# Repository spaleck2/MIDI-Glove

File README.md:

# MIDI-Glove
Eagle schematics and board layouts

This is a repository to share our schematics and board layouts so that we can help eachother out with design and each have access to all of the files.

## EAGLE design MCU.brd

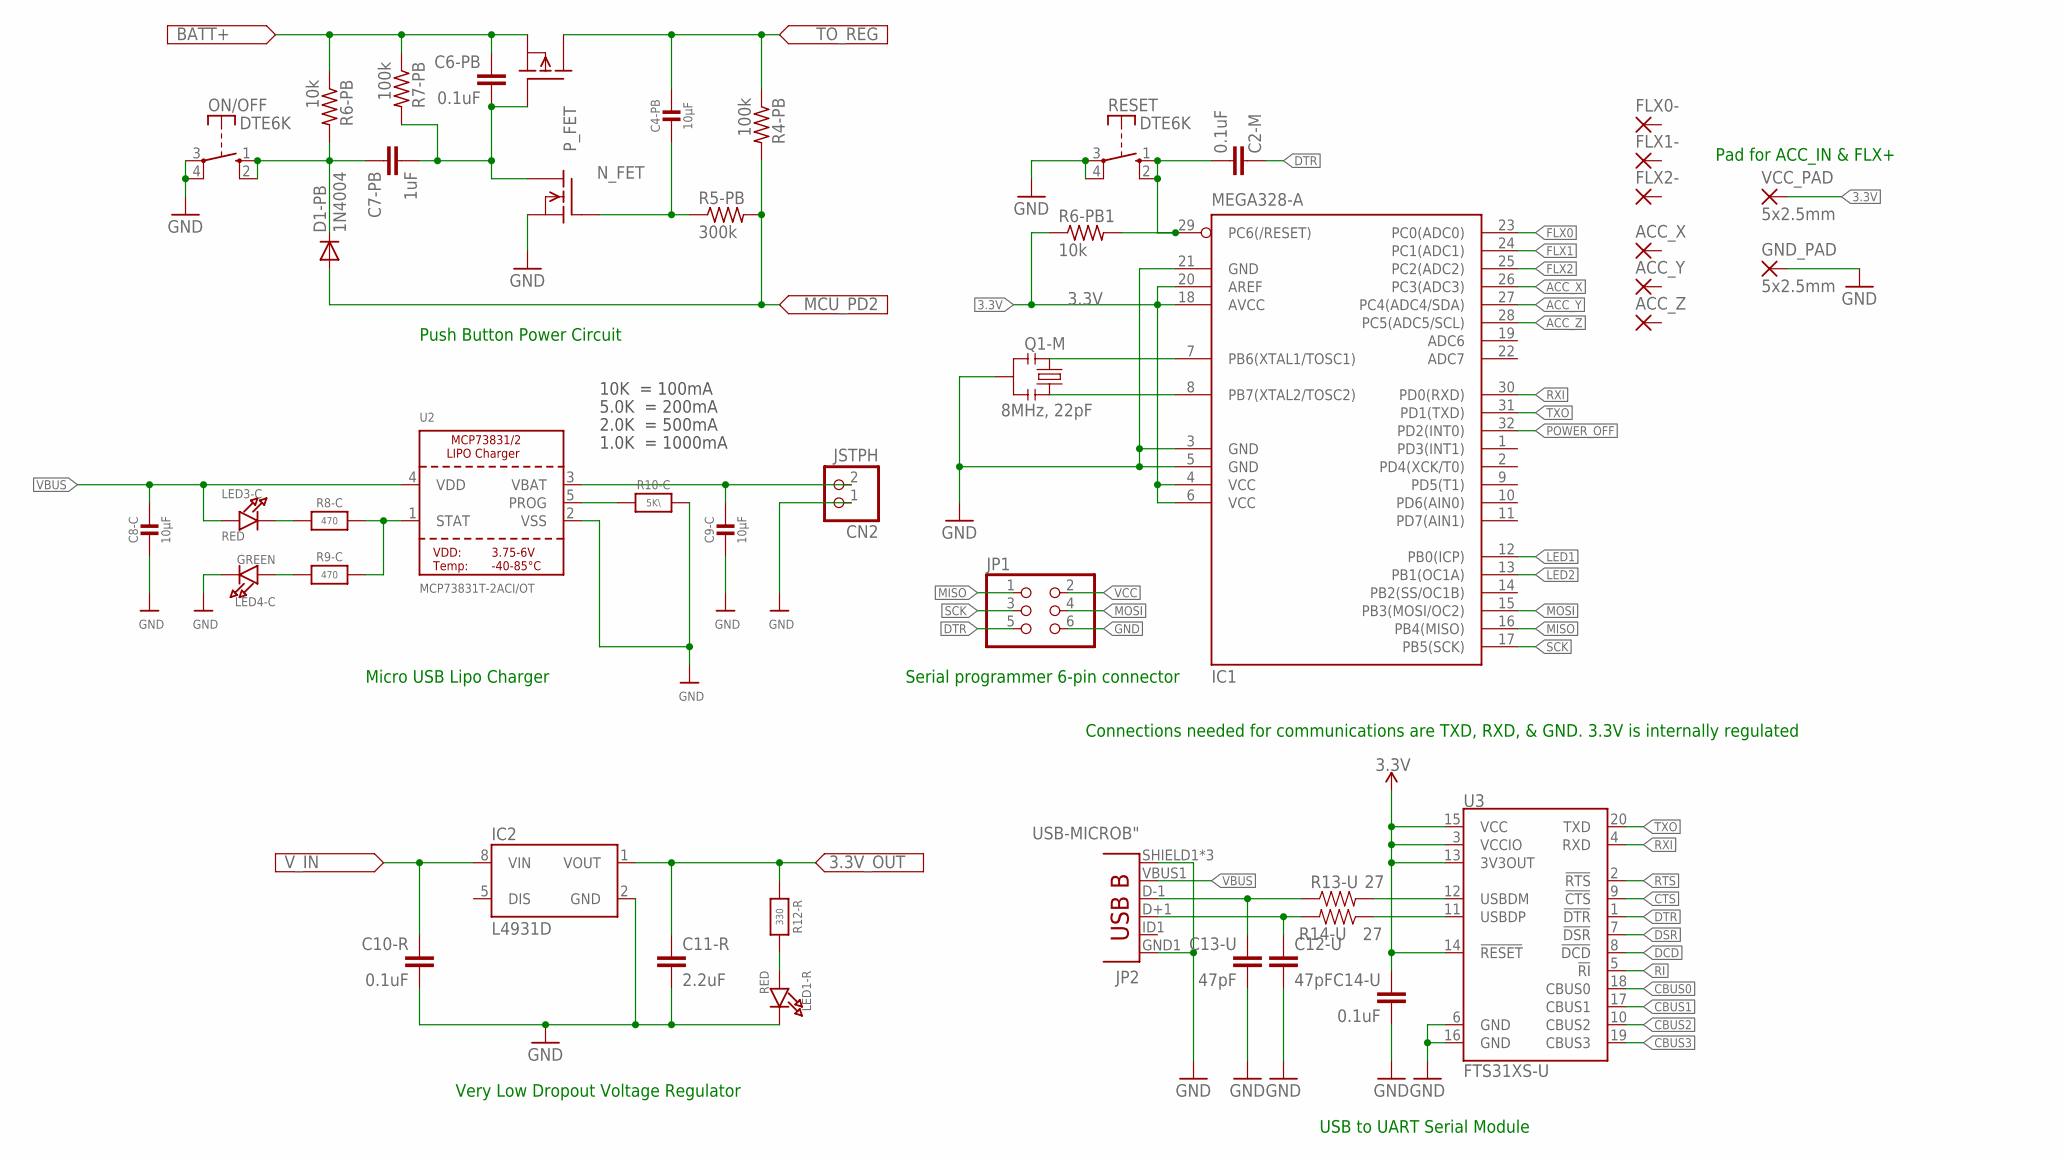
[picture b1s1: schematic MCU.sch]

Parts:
ACC_X: 1,6/0,8
ACC_Y: 1,6/0,8
ACC_Z: 1,6/0,8
C2-M, C6-PB, C10-R, C14-U: 0.1uF; 0603-CAP
C4-PB, C8-C, C9-C: 10µF; 0805-NO
C7-PB: 1uF; 0603-CAP
C11-R: 2.2uF; 0603-CAP
C12-U, C13-U: 47pF; 0603-CAP
CN2: JSTPH; JSTPH2
D1-PB: 1N4004; DO41-10
FLX0-, FLX1-, FLX2-: 1,6/0,8
GND_PAD: 5x2.5mm; 5-2,5
IC1: MEGA328-A; TQFP32-08
IC2: L4931D; SO08
JP1: PINHD-2X3; 2X03
JP2: USB-MICROB"; USB-B-MICRO-SMD_V03
LED1-R, LED3-C: RED; CHIPLED_0805_NOOUTLINE
LED4-C: GREEN; CHIPLED_0805_NOOUTLINE
N_FET: BSS101; TO92
ON/OFF: DTE6K
P_FET: BSS92; TO92
Q1-M: 8MHz, 22pF; RESONATOR-SMD-1:1
R4-PB, R7-PB: 100k; R0805
R5-PB: 300k; R0805
R6-PB, R6-PB1: 10k; R0805
R8-C, R9-C: 470; 0805-NO
R10-C: 5K\; 0805-NO
R12-R: 330; 0805-NO
R13-U, R14-U: 27; 0603-RES
RESET: DTE6K
U2: MCP73831T-2ACI/OT; SOT23-5
U3: FTS31XS-U; SSOP20_L
VCC_PAD: 5x2.5mm; 5-2,5

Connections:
3.3V: C11-R.1, C14-U.1, IC1.4 (VCC), IC1.6 (VCC), IC1.18 (AVCC), IC1.20 (AREF), IC2.1 (VOUT), R6-PB1.1, R12-R.1, U3.3 (VCCIO), U3.13 (3V3OUT), U3.14 (!RESET), U3.15 (VCC), VCC_PAD.1
ACC_X: IC1.26 (PC3(ADC3))
ACC_Y: IC1.27 (PC4(ADC4/SDA))
ACC_Z: IC1.28 (PC5(ADC5/SCL))
CBUS0: U3.18 (CBUS0)
CBUS3: U3.19 (CBUS3)
CTS: U3.9 (!CTS)
DCD: U3.8 (!DCD)
DSR: U3.7 (!DSR)
DTR: C2-M.2, JP1.5, U3.1 (!DTR)
FLX0: IC1.23 (PC0(ADC0))
FLX2: IC1.25 (PC2(ADC2))
FLX!: IC1.24 (PC1(ADC1))
GND: C8-C.2, C9-C.2, C10-R.2, C11-R.2, C12-U.2, C13-U.2, C14-U.2, CN2.1, GND_PAD.1, IC1.3 (GND), IC1.5 (GND), IC1.21 (GND), IC2.2 (GND), JP1.6, JP2.GND1 (GND), JP2.SHIELD1 (SHIELD), JP2.SHIELD2 (SHIELD), JP2.SHIELD3 (SHIELD), LED1-R.C, LED4-C.C, N_FET.1 (S), ON/OFF.3, ON/OFF.4, Q1-M.2, R10-C.2, RESET.3, RESET.4, U2.2 (VSS), U3.6 (GND), U3.16 (GND)
MISO: IC1.16 (PB4(MISO)), JP1.1
MOSI: IC1.15 (PB3(MOSI/OC2)), JP1.4
unnamed: R13-U.2, U3.12 (USBDM)
unnamed: C2-M.1, IC1.29 (PC6(/RESET)), R6-PB1.2, RESET.1 (S), RESET.2 (S)
unnamed: IC1.7 (PB6(XTAL1/TOSC1)), Q1-M.1
unnamed: IC1.8 (PB7(XTAL2/TOSC2)), Q1-M.3
unnamed: C7-PB.1, D1-PB.C, ON/OFF.1 (S), ON/OFF.2 (S), R6-PB.2
unnamed: LED1-R.A, R12-R.2
unnamed: C4-PB.2, N_FET.2 (G), R5-PB.1
unnamed: R14-U.1, U3.11 (USBDP)
unnamed: C12-U.1, JP2.D+1 (D+), R14-U.2
unnamed: C6-PB.2, C7-PB.2, N_FET.3 (D), P_FET.1 (G), R7-PB.2
unnamed: LED3-C.C, R8-C.1
unnamed: R8-C.2, R9-C.2, U2.1 (STAT)
unnamed: R10-C.1, U2.5 (PROG)
unnamed: LED4-C.A, R9-C.1
unnamed: C13-U.1, JP2.D-1 (D-), R13-U.1
POWER_OFF: D1-PB.A, IC1.32 (PD2(INT0)), R4-PB.2, R5-PB.2
RI: U3.5 (!RI)
RTS: U3.2 (!RTS)
RXI: IC1.30 (PD0(RXD)), U3.4 (RXD)
SCK: IC1.17 (PB5(SCK)), JP1.3
TXO: IC1.31 (PD1(TXD)), U3.20 (TXD)
VBAT: C6-PB.1, C9-C.1, CN2.2, P_FET.3 (S), R6-PB.1, R7-PB.1, U2.3 (VBAT)
VBUS: C8-C.1, JP2.VBUS1 (VBUS), LED3-C.A, U2.4 (VDD)
VCC: JP1.2
V_IN: C4-PB.1, C10-R.1, IC2.8 (VIN), P_FET.2 (D), R4-PB.1

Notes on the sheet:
Serial programmer 6-pin connector
Pad for ACC_IN & FLX+
Connections needed for communications are TXD, RXD, & GND. 3.3V is internally regulated
10K = 100mA
5.0K = 200mA
2.0K = 500mA
1.0K = 1000mA
USB to UART Serial Module
Very Low Dropout Voltage Regulator
Micro USB Lipo Charger
Push Button Power Circuit

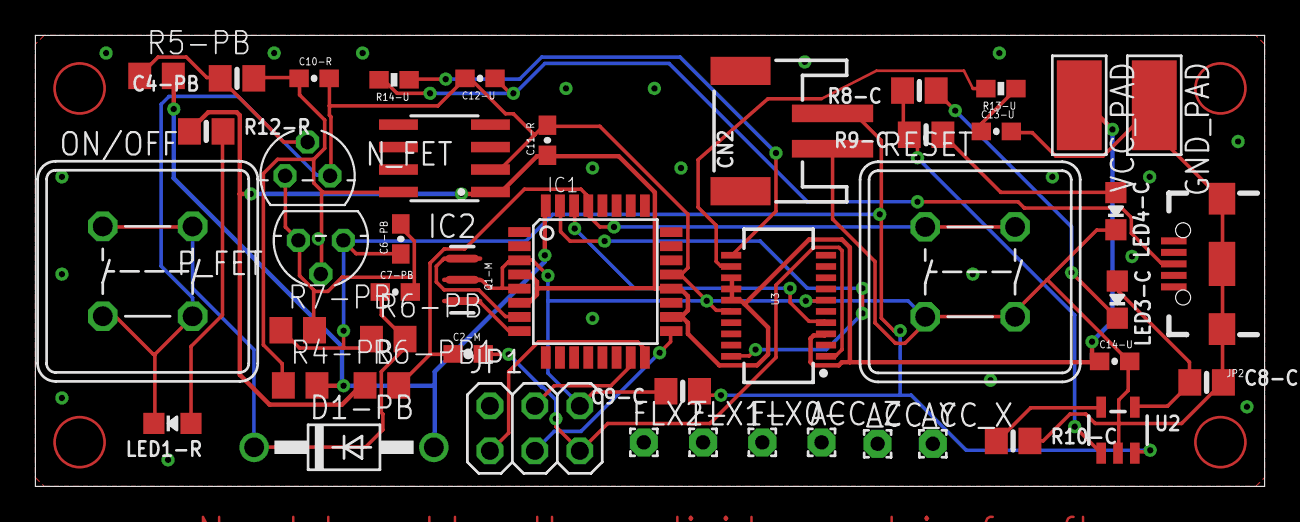
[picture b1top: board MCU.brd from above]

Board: 2 copper layers, 69.5 x 25.5 mm, 46 parts (0 on the bottom side), 27 nets.

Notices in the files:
parts and their libraries:
SparkFun-Capacitors: Licensing: CC v3.0 Share-Alike You are welcome to use this library for commercial purposes.
microbuilder: This work is placed in the public domain, and may be freely used for commercial and non-commercial work with the following conditions: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
